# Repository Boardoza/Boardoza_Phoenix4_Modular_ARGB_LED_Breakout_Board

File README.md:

# Boardoza Phoenix4 Breakout Board

The **Boardoza Phoenix4** is a modular addressable RGB LED breakout board designed to help makers create custom lighting patterns with maximum flexibility. Built around **addressable RGB LEDs**, this board integrates four addressable RGB LED segments in a compact and daisy-chain form factor.

The board allows multiple units to be soldered together to form letters, numbers, symbols, or custom lighting shapes. It supports both **3.3V and 5V power supplies** and is compatible with a wide range of microcontrollers and digital systems. The **Boardoza Phoenix4** is suitable for decorative lighting, interactive displays, prototypes, and general-purpose addressable LED applications.

## [Click here to purchase!](https://www.ozdisan.com/ureticiler/boardoza)

| Front Side | Back Side |
|-----------|-----------|
|  |  |

---

## Key Features

- **Modular ARGB Lighting Design:** Allows multiple boards to be soldered together to create letters, numbers, or custom shapes.
- **Addressable RGB LEDs:** Each LED can be individually controlled for precise color and brightness adjustments.
- **Wide Voltage Compatibility:** Supports both **3.3V and 5V** power supplies for broad microcontroller compatibility.
- **TTL & CMOS Logic Support:** Ensures seamless operation with different digital logic levels.
- **Expandable Structure:** Designed for daisy-chaining to build larger and more complex lighting systems.

---

## Technical Specifications

**Model:** Phoenix4   
**Manufacturer:** Boardoza  
**Functions:** Addressable RGB LED Lighting Board  
**Input Voltage:** 3.3 V / 5 V  
**LED Model:** T3A33BRG-H9C0002X1U1930  
**Number of LEDs:** 24   
**LED Type:** Individually addressable RGB LEDs  
**Logic Compatibility:** TTL & CMOS  
**Data Interface:** Serial Data & Clock (DIN / CIN / DOUT / COUT)  
**Daisy-Chain Support:** Yes  
**Operating Temperature:** -40 °C to +85 °C  
**Board Dimensions:** 6.9 mm × 34 mm  

---

## Board Pinout

### ( J1 ) Output Connector

| Pin Number | Pin Name | Description |
| --- | --- | --- |
| 1 | VCC | Power Supply |
| 2 | COUT | Clock Output |
| 3 | DOUT | Data Output |
| 4 | GND | Ground |

### ( J2 ) Input Connector

| Pin Number | Pin Name | Description |
| --- | --- | --- |
| 1 | VCC | Power Supply |
| 2 | CIN | Clock Input |
| 3 | DIN | Data Input |
| 4 | GND | Ground |

---

## Board Dimensions

---

## Step Files

[Boardoza Phoenix4.step](./assets/Phoenix4%20Step.step)

---

## Sensor Datasheet

[T3A33BRG Datasheet.pdf](./assets/Phoenix4%20Datasheet.pdf)

---

## Version History

- **V1.0.0** – Initial Release

---

## Support

- If you have any questions or need support, please contact **support@boardoza.com**

---

## **License**

This repository contains both hardware and software components:

### **Hardware Design**

[![CC BY-SA 4.0][cc-by-sa-shield]][cc-by-sa]

All hardware design files are licensed under [Creative Commons Attribution-ShareAlike 4.0 International License][cc-by-sa].

[cc-by-sa]: http://creativecommons.org/licenses/by-sa/4.0/
[cc-by-sa-shield]: https://img.shields.io/badge/License-CC%20BY--SA%204.0-lightgrey.svg

### **Software/Firmware**

[![BSD-3-Clause][bsd-shield]][bsd]

All software and firmware are licensed under [BSD 3-Clause License][bsd].

[bsd]: https://opensource.org/licenses/BSD-3-Clause
[bsd-shield]: https://img.shields.io/badge/License-BSD%203--Clause-blue.svg

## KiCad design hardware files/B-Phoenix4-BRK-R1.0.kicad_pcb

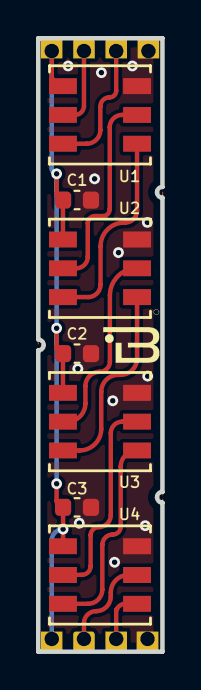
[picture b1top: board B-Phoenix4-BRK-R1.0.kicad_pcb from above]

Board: 2 copper layers, 6.9 x 34.1 mm, 15 parts (0 on the bottom side), 12 nets.

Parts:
C1, C2, C3: 100nF; C_0603_1608Metric
J1, J2, J3, J4, J5, J6, J7, J8: Conn_01x01_Pin; PinHeader_1x01_P2.54mm_Vertical
U1, U2, U3, U4: T3A33BRG-H9C0002X1U1930_HVK

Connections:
/CIN: J8.1, U4.5 (CIN)
/COUT: J5.1, U1.2 (COUT)
/DIN: J7.1, U4.4 (DIN)
/DOUT: J6.1, U1.3 (DOUT)
GND: C1.1, C2.1, C3.1, J3.1, J4.1, U1.6 (GND), U2.6 (GND), U3.6 (GND), U4.6 (GND)
unnamed: U1.5 (CIN), U2.2 (COUT)
unnamed: U1.4 (DIN), U2.3 (DOUT)
unnamed: U2.5 (CIN), U3.2 (COUT)
unnamed: U2.4 (DIN), U3.3 (DOUT)
unnamed: U3.5 (CIN), U4.2 (COUT)
unnamed: U3.4 (DIN), U4.3 (DOUT)
VCC: C1.2, C2.2, C3.2, J1.1, J2.1, U1.1 (VDD), U2.1 (VDD), U3.1 (VDD), U4.1 (VDD)

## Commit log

2026-04-28 Fix formatting of hueOffset declaration
2026-04-28 Fixed comment lines
